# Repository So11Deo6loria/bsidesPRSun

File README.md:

# BSidesPR Taino Sun
Welcome to BSides Puerto Rico 2024!!! We were happy to have the opportunity to create this year's badge! 

# Functionality
The badge has a default color pattern but we made it highly configurable on purpose. We would love to see all the custom color schemes that people come up with! Come see us to learn more about how you can modify the badge! 

# Troubleshooting
Come find one of the makers on the back of the badge if you have any issues. We will be speaking in the Main Hall (104 B & C) from 1405-1435 on Friday and conducting workshops in 102B on Saturday from 1010-1125. 

Please note that if the badge is running consistently, the battery life will be limited.

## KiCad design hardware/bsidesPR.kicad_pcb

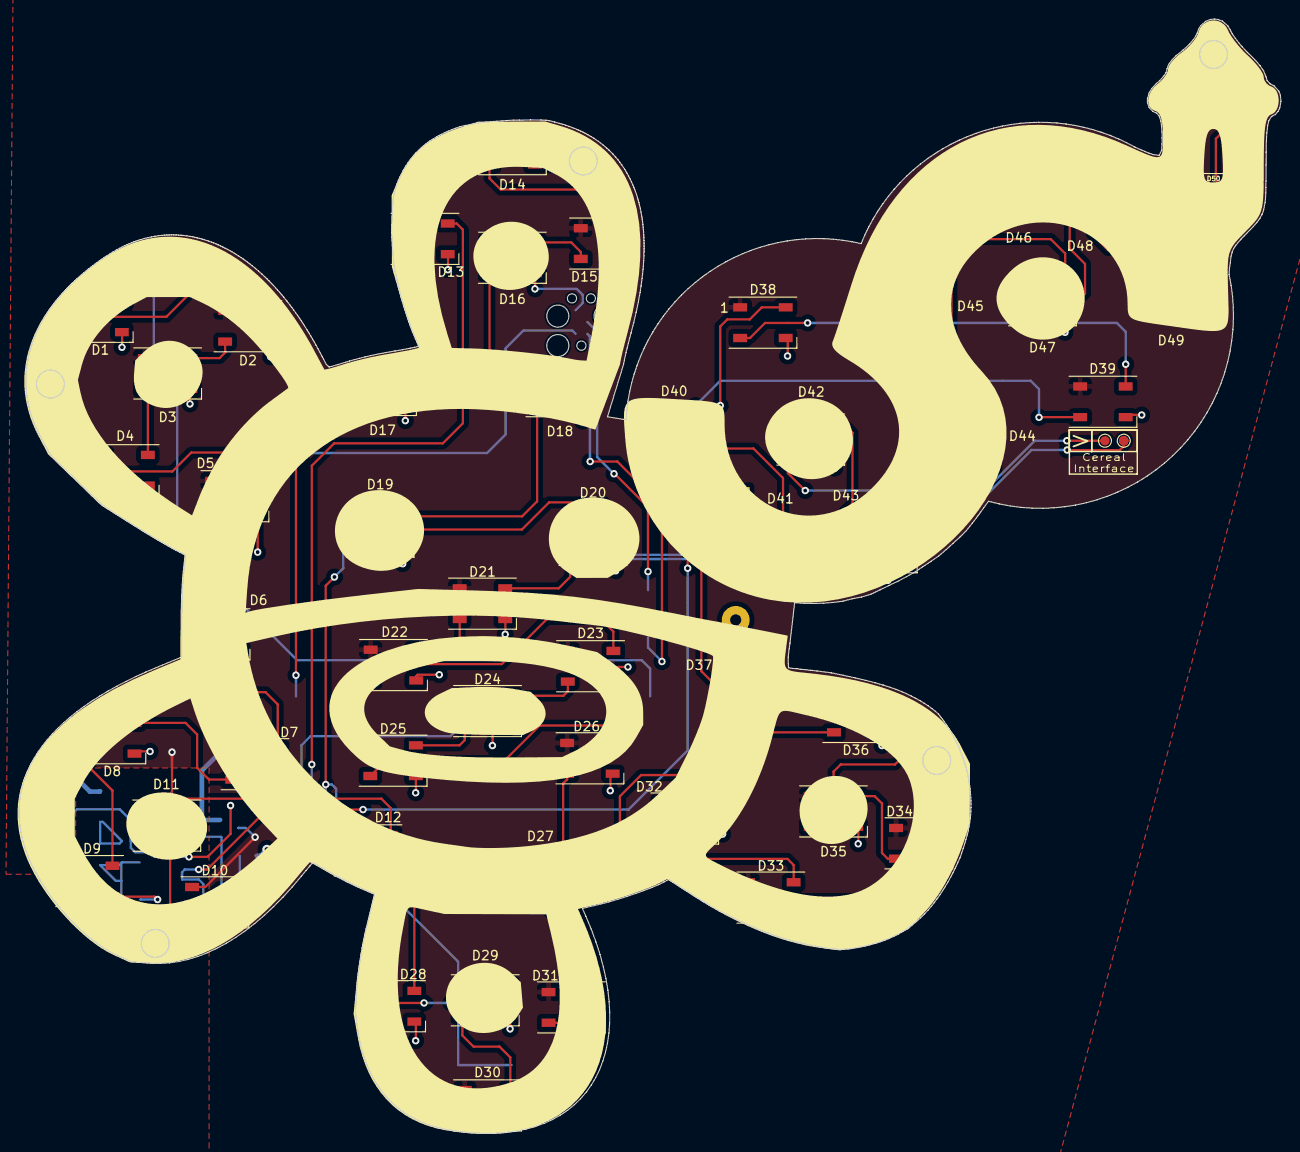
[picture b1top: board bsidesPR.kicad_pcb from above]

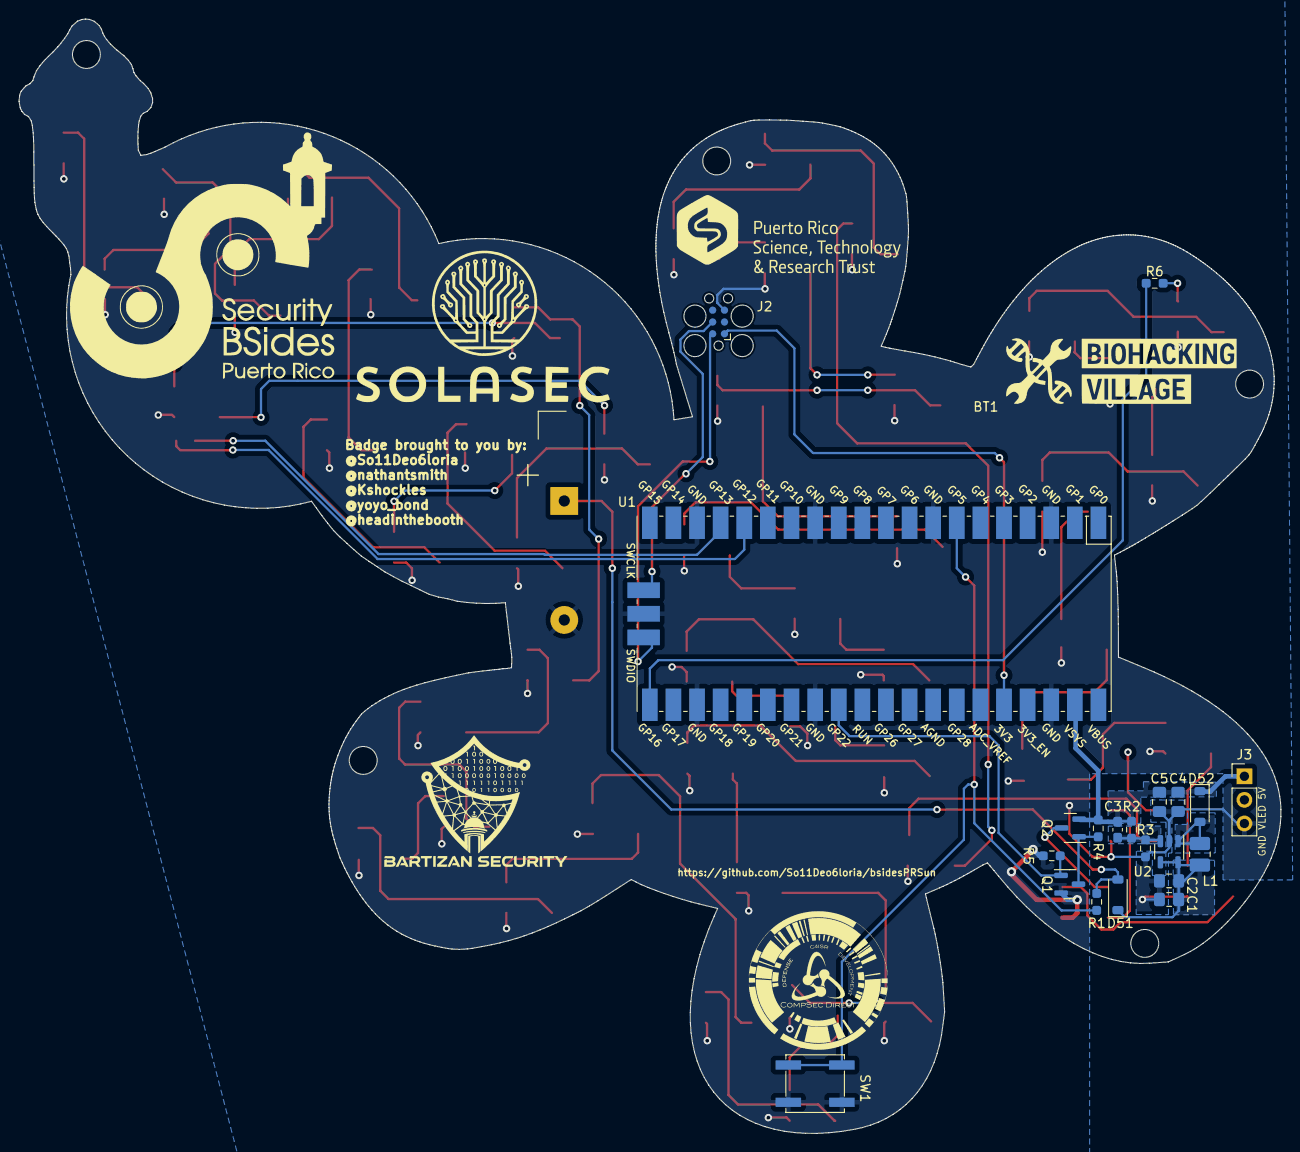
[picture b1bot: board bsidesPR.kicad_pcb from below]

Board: 2 copper layers, 135.8 x 119.9 mm, 72 parts (22 on the bottom side), 64 nets.

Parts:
BT1: Battery; BatteryHolder_TruPower_BH-331P_3xAA
C1, C2, C4, C5: 4.7uF; C_0805_2012Metric_Pad1.18x1.45mm_HandSolder
C3: 3.3pF; C_0603_1608Metric_Pad1.08x0.95mm_HandSolder
D1, D2, D3, D4, D5, D6, D7, D8, D9, D10, D11, D12, D13, D14, D15, D16, D17, D18, D19, D20, D21, D22, D23, D24, D25, D26, D27, D28, D29, D30, D31, D32, D33, D34, D35, D36, D37, D38, D39, D40, D41, D42, D43, D44, D45, D46, D47, D48, D49, D50: WS2812B; LED_WS2812B_PLCC4_5.0x5.0mm_P3.2mm
D51, D52: BAT54W-HG3-18; D_SOD-123
J2: Conn_ARM_SWD_TagConnect_TC2030; Tag-Connect_TC2030-IDC-FP_2x03_P1.27mm_Vertical
J3: Conn_01x03_Female; PinHeader_1x03_P2.54mm_Vertical
L1: 3.3uH; L_1008_2520Metric_Pad1.43x2.20mm_HandSolder
Q1: 2N7002H; SOT-23
Q2: DMP2012SN-7; SOT-23
R1, R4, R5: 10k; R_0603_1608Metric_Pad0.98x0.95mm_HandSolder
R2: 620k; R_0603_1608Metric_Pad0.98x0.95mm_HandSolder
R3: 200k; R_0603_1608Metric_Pad0.98x0.95mm_HandSolder
R6: 500; R_0603_1608Metric_Pad0.98x0.95mm_HandSolder
SW1: SW_MEC_5G; SW_SPST_EVPBF
U1: Pico; RPi_Pico_SMD_TH
U2: TPS61040DDC; SOT-23-5

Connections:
+3V3: J2.1 (VCC), U1.36 (3V3)
+5V: C3.1, C4.1, C5.1, D52.1 (K), J3.1, Q2.2 (S), R2.1, R4.1, U1.39 (VSYS)
/EN: C1.1, C2.1, D51.1 (K), L1.1, U2.4 (EN), U2.5 (VIN)
/FB: C3.2, R2.2, R3.1, U2.3 (FB)
/SW: D52.2 (A), L1.2, U2.1 (SW)
ENABLE_VLED: Q1.1 (G), R5.1, U1.29 (GPIO22)
GND: BT1.2 (-), C1.2, C2.2, C4.2, C5.2, D1.3 (VSS), D2.3 (VSS), D3.3 (VSS), D4.3 (VSS), D5.3 (VSS), D6.3 (VSS), D7.3 (VSS), D8.3 (VSS), D9.3 (VSS), D10.3 (VSS), D11.3 (VSS), D12.3 (VSS), D13.3 (VSS), D14.3 (VSS), D15.3 (VSS), D16.3 (VSS), D17.3 (VSS), D18.3 (VSS), D19.3 (VSS), D20.3 (VSS), D21.3 (VSS), D22.3 (VSS), D23.3 (VSS), D24.3 (VSS), D25.3 (VSS), D26.3 (VSS), D27.3 (VSS), D28.3 (VSS), D29.3 (VSS), D30.3 (VSS), D31.3 (VSS), D32.3 (VSS), D33.3 (VSS), D34.3 (VSS), D35.3 (VSS), D36.3 (VSS), D37.3 (VSS), D38.3 (VSS), D39.3 (VSS), D40.3 (VSS), D41.3 (VSS), D42.3 (VSS), D43.3 (VSS), D44.3 (VSS), D45.3 (VSS), D46.3 (VSS), D47.3 (VSS), D48.3 (VSS), D49.3 (VSS), D50.3 (VSS), J2.5 (GND), J3.3, Q1.2 (S), R3.2, R5.2, SW1.2 (B), SW1.4 (B), U1.3 (GND), U1.8 (GND), U1.13 (GND), U1.18 (GND), U1.23 (GND), U1.28 (GND), U1.38 (GND), U1.42 (GND), U2.2 (GND)
LED_PIN: R6.1, U1.21 (GPIO16)
unnamed: BT1.1 (+), D51.2 (A), R1.1
unnamed: D1.4 (DIN), R6.2
unnamed: D1.2 (DOUT), D2.4 (DIN)
unnamed: D2.2 (DOUT), D3.4 (DIN)
unnamed: D3.2 (DOUT), D4.4 (DIN)
unnamed: D4.2 (DOUT), D5.4 (DIN)
unnamed: D5.2 (DOUT), D6.4 (DIN)
unnamed: D6.2 (DOUT), D7.4 (DIN)
unnamed: D7.2 (DOUT), D8.4 (DIN)
unnamed: D8.2 (DOUT), D9.4 (DIN)
unnamed: D9.2 (DOUT), D10.4 (DIN)
unnamed: D10.2 (DOUT), D11.4 (DIN)
unnamed: D11.2 (DOUT), D12.4 (DIN)
unnamed: D12.2 (DOUT), D13.4 (DIN)
unnamed: D13.2 (DOUT), D14.4 (DIN)
unnamed: D14.2 (DOUT), D15.4 (DIN)
unnamed: D15.2 (DOUT), D16.4 (DIN)
unnamed: D16.2 (DOUT), D17.4 (DIN)
unnamed: D17.2 (DOUT), D18.4 (DIN)
unnamed: D18.2 (DOUT), D19.4 (DIN)
unnamed: D19.2 (DOUT), D20.4 (DIN)
unnamed: D20.2 (DOUT), D21.4 (DIN)
unnamed: D21.2 (DOUT), D22.4 (DIN)
unnamed: D22.2 (DOUT), D23.4 (DIN)
unnamed: D23.2 (DOUT), D24.4 (DIN)
unnamed: D24.2 (DOUT), D25.4 (DIN)
unnamed: D25.2 (DOUT), D26.4 (DIN)
unnamed: D26.2 (DOUT), D27.4 (DIN)
unnamed: D27.2 (DOUT), D28.4 (DIN)
unnamed: D28.2 (DOUT), D29.4 (DIN)
unnamed: D29.2 (DOUT), D30.4 (DIN)
unnamed: D30.2 (DOUT), D31.4 (DIN)
unnamed: D31.2 (DOUT), D32.4 (DIN)
unnamed: D32.2 (DOUT), D33.4 (DIN)
unnamed: D33.2 (DOUT), D34.4 (DIN)
unnamed: D34.2 (DOUT), D35.4 (DIN)
unnamed: D35.2 (DOUT), D36.4 (DIN)
unnamed: D36.2 (DOUT), D37.4 (DIN)
unnamed: D37.2 (DOUT), D38.4 (DIN)
unnamed: D38.2 (DOUT), D39.4 (DIN)
unnamed: D39.2 (DOUT), D40.4 (DIN)
unnamed: D40.2 (DOUT), D41.4 (DIN)
unnamed: D41.2 (DOUT), D42.4 (DIN)
unnamed: D42.2 (DOUT), D43.4 (DIN)
unnamed: D43.2 (DOUT), D44.4 (DIN)
unnamed: D44.2 (DOUT), D45.4 (DIN)
unnamed: D45.2 (DOUT), D46.4 (DIN)
unnamed: D46.2 (DOUT), D47.4 (DIN)
unnamed: D47.2 (DOUT), D48.4 (DIN)
unnamed: D48.2 (DOUT), D49.4 (DIN)
unnamed: D49.2 (DOUT), D50.4 (DIN)
unnamed: J2.4 (SWCLK), U1.41 (SWCLK)
unnamed: J2.2 (SWDIO), U1.43 (SWDIO)
unnamed: Q1.3 (D), Q2.1 (G), R4.2
RPi_WAKE: R1.2, SW1.1 (A), U1.7 (GPIO5)
VLED: D1.1 (VDD), D2.1 (VDD), D3.1 (VDD), D4.1 (VDD), D5.1 (VDD), D6.1 (VDD), D7.1 (VDD), D8.1 (VDD), D9.1 (VDD), D10.1 (VDD), D11.1 (VDD), D12.1 (VDD), D13.1 (VDD), D14.1 (VDD), D15.1 (VDD), D16.1 (VDD), D17.1 (VDD), D18.1 (VDD), D19.1 (VDD), D20.1 (VDD), D21.1 (VDD), D22.1 (VDD), D23.1 (VDD), D24.1 (VDD), D25.1 (VDD), D26.1 (VDD), D27.1 (VDD), D28.1 (VDD), D29.1 (VDD), D30.1 (VDD), D31.1 (VDD), D32.1 (VDD), D33.1 (VDD), D34.1 (VDD), D35.1 (VDD), D36.1 (VDD), D37.1 (VDD), D38.1 (VDD), D39.1 (VDD), D40.1 (VDD), D41.1 (VDD), D42.1 (VDD), D43.1 (VDD), D44.1 (VDD), D45.1 (VDD), D46.1 (VDD), D47.1 (VDD), D48.1 (VDD), D49.1 (VDD), D50.1 (VDD), J3.2, Q2.3 (D)

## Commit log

2024-01-31 Initial code and hardware commit
2024-02-25 Adding some animation support as well as final hardware files
2024-02-28 Making minor flow modifications
2024-03-10 go for broke
2024-03-10 baseline the animation
2024-03-10 tuned the waving animation
2024-03-16 updated interface
2024-03-22 Firmware is close. We just need to add the flags, test one more time, and add back the lowpower stuff that messes with rshell.
2024-03-23 Firmware is good minus the low power stuff I will add tomorrow morning. Nate feel free to rewrite it all tonight
2024-03-23 Updated Wave Constants based on physical LED placement.
2024-03-23 Added the lowpower code plus the ability to change the startup color
2024-03-23 This is Nates way
2024-04-09 Create LICENSE
2024-04-12 Update README.md
    Added Picture
